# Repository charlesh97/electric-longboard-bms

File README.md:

# Electric Longboard

Archived project. 

Latest revision PDFs
[Schematic](https://gitlab.com/chood2/electric-longboard-bms/-/blob/main/HW/LongboardGaugev2%20SCH.pdf)
[PCB](https://gitlab.com/chood2/electric-longboard-bms/-/blob/main/HW/LongboardGaugev2%20PCB.pdf)

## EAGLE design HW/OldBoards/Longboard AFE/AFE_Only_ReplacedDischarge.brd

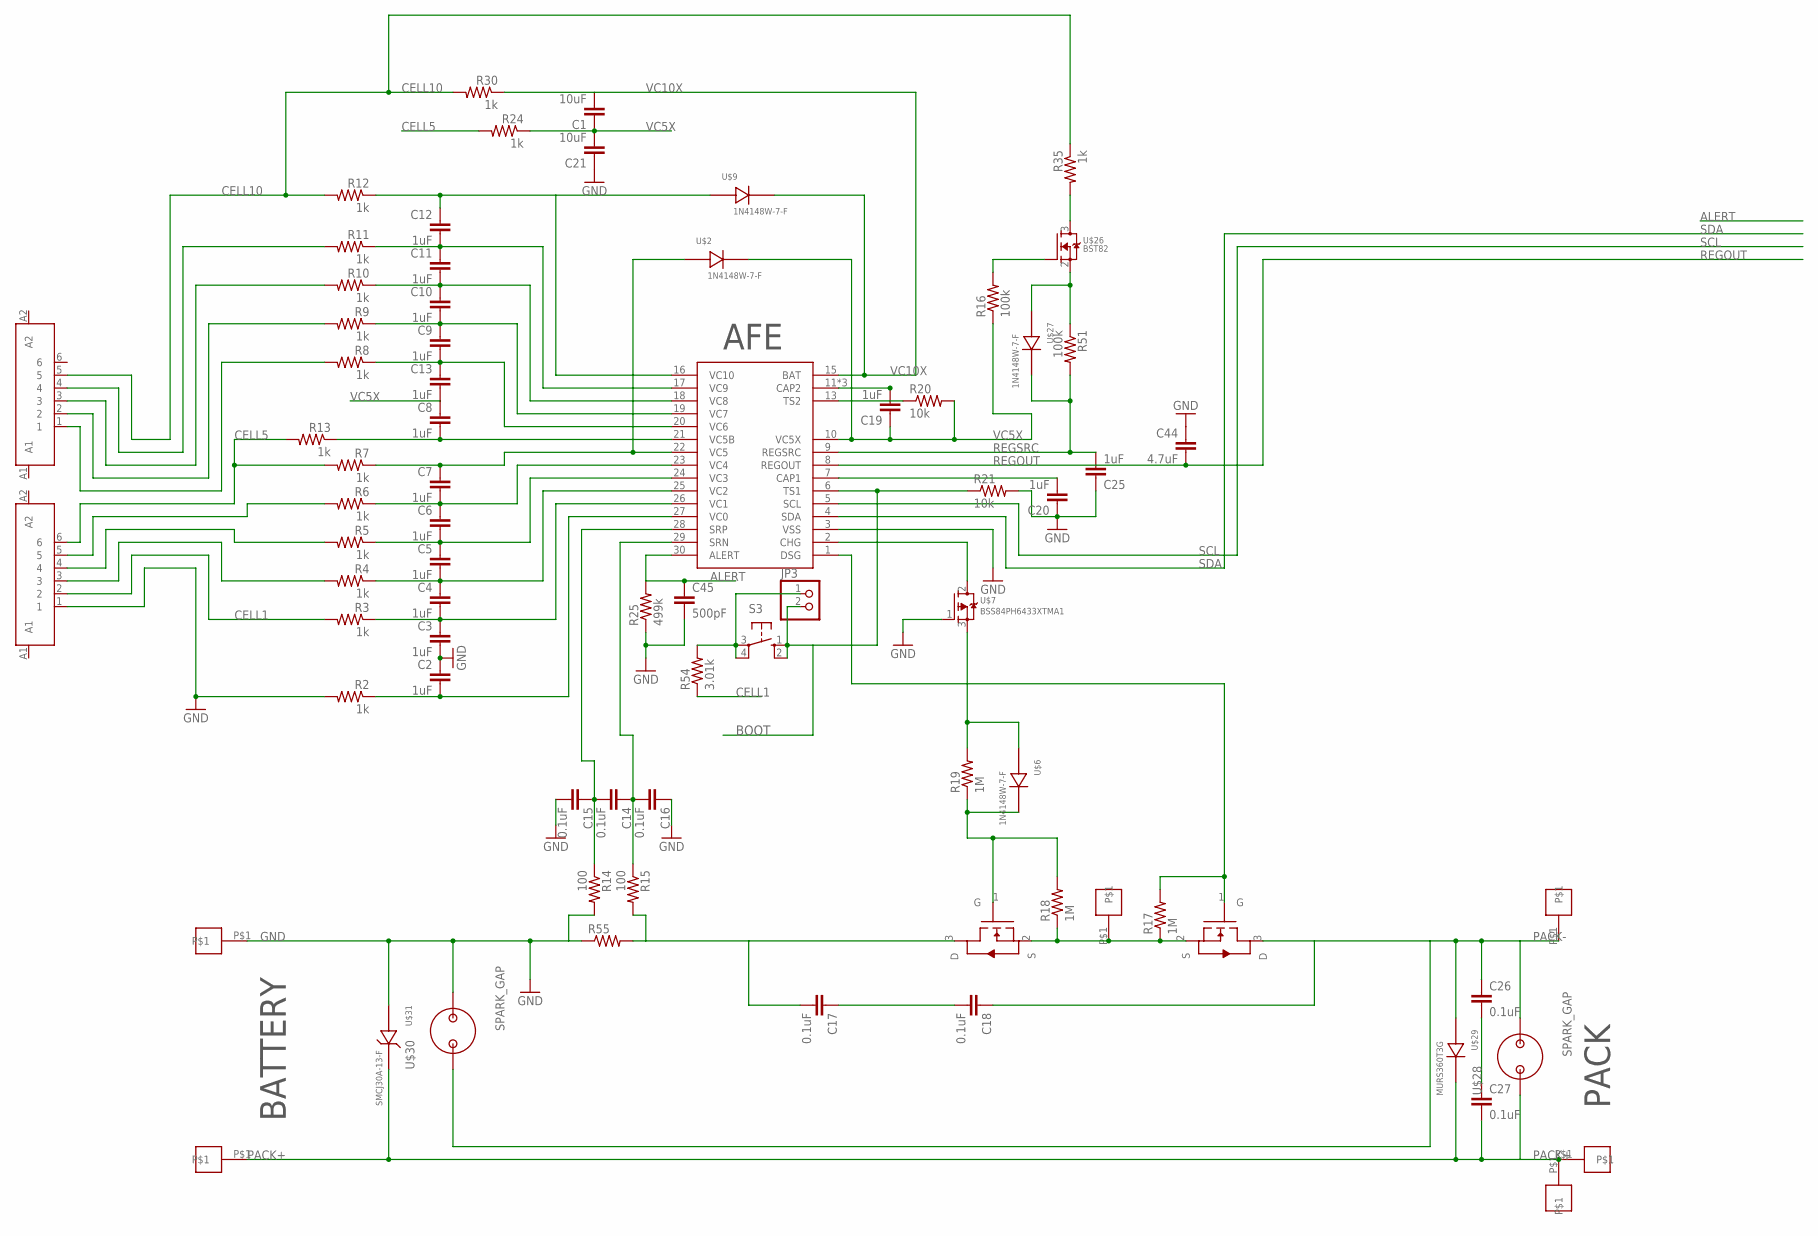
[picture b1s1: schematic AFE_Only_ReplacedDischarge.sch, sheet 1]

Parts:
C1, C21: 10uF; C1210
C2, C3, C4, C5, C6, C7, C8, C9, C10, C11, C12, C13, C19, C20, C25: 1uF; C0805
C14, C15, C16, C17, C18, C26, C27: 0.1uF; C0805
C44: 4.7uF; C0805
C45: 500pF; C0603
JP3: PINHD-1X2; 1X02
R2, R3, R4, R5, R6, R7, R8, R9, R10, R11, R12, R13, R24, R30, R35: 1k; R1206
R14, R15: 100; R0805
R16, R51: 100k; R0805
R17, R18, R19: 1M; R1206
R20, R21: 10k; R0805
R25: 499k; R0603
R54: 3.01k; R1206
R55: R-US_R2512; R2512
S3: 10-XX; B3F-10XX
U$1: BQ76930; SOIC-30
U$2, U$6, U$9, U$27: 1N4148W-7-F; SOD-123
U$3, U$35, U$36, U$37, U$38, U$39: PAD
U$4, U$5: AOB290L; TO-263
U$7: BSS84PH6433XTMA1; SOT23-3
U$24, U$33: JST_6PIN
U$26: BST82; SOT23-3
U$28, U$30: SPARK_GAP
U$29: MURS360T3G; SMC(DO-214AB)
U$31: SMCJ30A-13-F; SMB(DO-214AA)

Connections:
ALERT: C45.1, R25.2, U$1.30 (ALERT); also elsewhere on the board
BOOT: JP3.2, R21.1, S3.1 (S), S3.2 (S1), U$1.6 (TS1)
CELL1: R3.2, R54.1, U$33.2
CELL5: R7.2, R13.2, R24.2, U$33.6
CELL10: R12.2, R30.2, R35.1, U$24.5
CHARGE-: R17.1, R18.1, U$4.2 (S), U$5.2 (S), U$37.P$1
GND: C2.1, C3.2, C15.2, C16.1, C20.1, C21.1, C25.1, C44.1, C45.2, R2.2, R14.2, R21.2, R25.1, R55.1, U$1.3 (VSS), U$3.P$1, U$7.1 (G), U$30.P$2, U$31.P$1 (1), U$33.1; also elsewhere on the board
unnamed: C3.1, C4.2, R3.1, U$1.26 (VC1)
unnamed: C4.1, C5.2, R4.1, U$1.25 (VC2)
unnamed: C5.1, C6.2, R5.1, U$1.24 (VC3)
unnamed: C6.1, C7.2, R6.1, U$1.23 (VC4)
unnamed: C7.1, R7.1, U$1.22 (VC5), U$2.P$1
unnamed: C8.2, R13.1, U$1.21 (VC5B)
unnamed: C9.1, C10.2, R9.1, U$1.19 (VC7)
unnamed: C10.1, C11.2, R10.1, U$1.18 (VC8)
unnamed: C11.1, C12.2, R11.1, U$1.17 (VC9)
unnamed: C12.1, R12.1, U$1.16 (VC10), U$9.P$1
unnamed: R5.2, U$33.4
unnamed: C2.2, R2.1, U$1.27 (VC0)
unnamed: C26.2, C27.1
unnamed: R4.2, U$33.3
unnamed: R6.2, U$33.5
unnamed: R8.2, U$24.1
unnamed: R9.2, U$24.2
unnamed: R10.2, U$24.3
unnamed: R11.2, U$24.4
unnamed: C9.2, C13.1, R8.1, U$1.20 (VC6)
unnamed: R16.2, U$26.1 (G)
unnamed: C20.2, U$1.7 (CAP1)
unnamed: C14.1, C16.2, R15.1, U$1.29 (SRN)
unnamed: JP3.1, R54.2, S3.3, S3.4 (P1)
unnamed: C14.2, C15.1, R14.1, U$1.28 (SRP)
unnamed: R18.2, R19.1, U$5.1 (G), U$6.P$2
unnamed: R19.2, U$6.P$1, U$7.3 (D)
unnamed: U$1.2 (CHG), U$7.2 (S)
unnamed: C17.1, C18.2
unnamed: C19.2, U$1.11 (CAP2), U$1.12 (CAP2), U$1.14 (CAP2)
unnamed: R20.1, U$1.13 (TS2)
unnamed: C17.2, R15.2, R55.2, U$5.3 (D)
unnamed: R17.2, U$1.1 (DSG), U$4.1 (G)
unnamed: R51.1, U$26.2 (S), U$27.P$1
unnamed: R35.2, U$26.3 (D)
PACK+: C27.2, U$28.P$1, U$29.2, U$31.P$2 (2), U$35.P$1, U$36.P$1, U$39.P$1
PACK-: C18.1, C26.1, U$4.3 (D), U$28.P$2, U$29.1, U$30.P$1, U$38.P$1
REGOUT: C44.2, U$1.8 (REGOUT); also elsewhere on the board
REGSRC: C25.2, R51.2, U$1.9 (REGSRC), U$27.P$2
SCL: U$1.5 (SCL); also elsewhere on the board
SDA: U$1.4 (SDA); also elsewhere on the board
VC5X: C1.1, C8.1, C13.2, C19.1, C21.2, R16.1, R20.2, R24.1, U$1.10 (VC5X), U$2.P$2
VC10X: C1.2, R30.1, U$1.15 (BAT), U$9.P$2

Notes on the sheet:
BATTERY
PACK
AFE

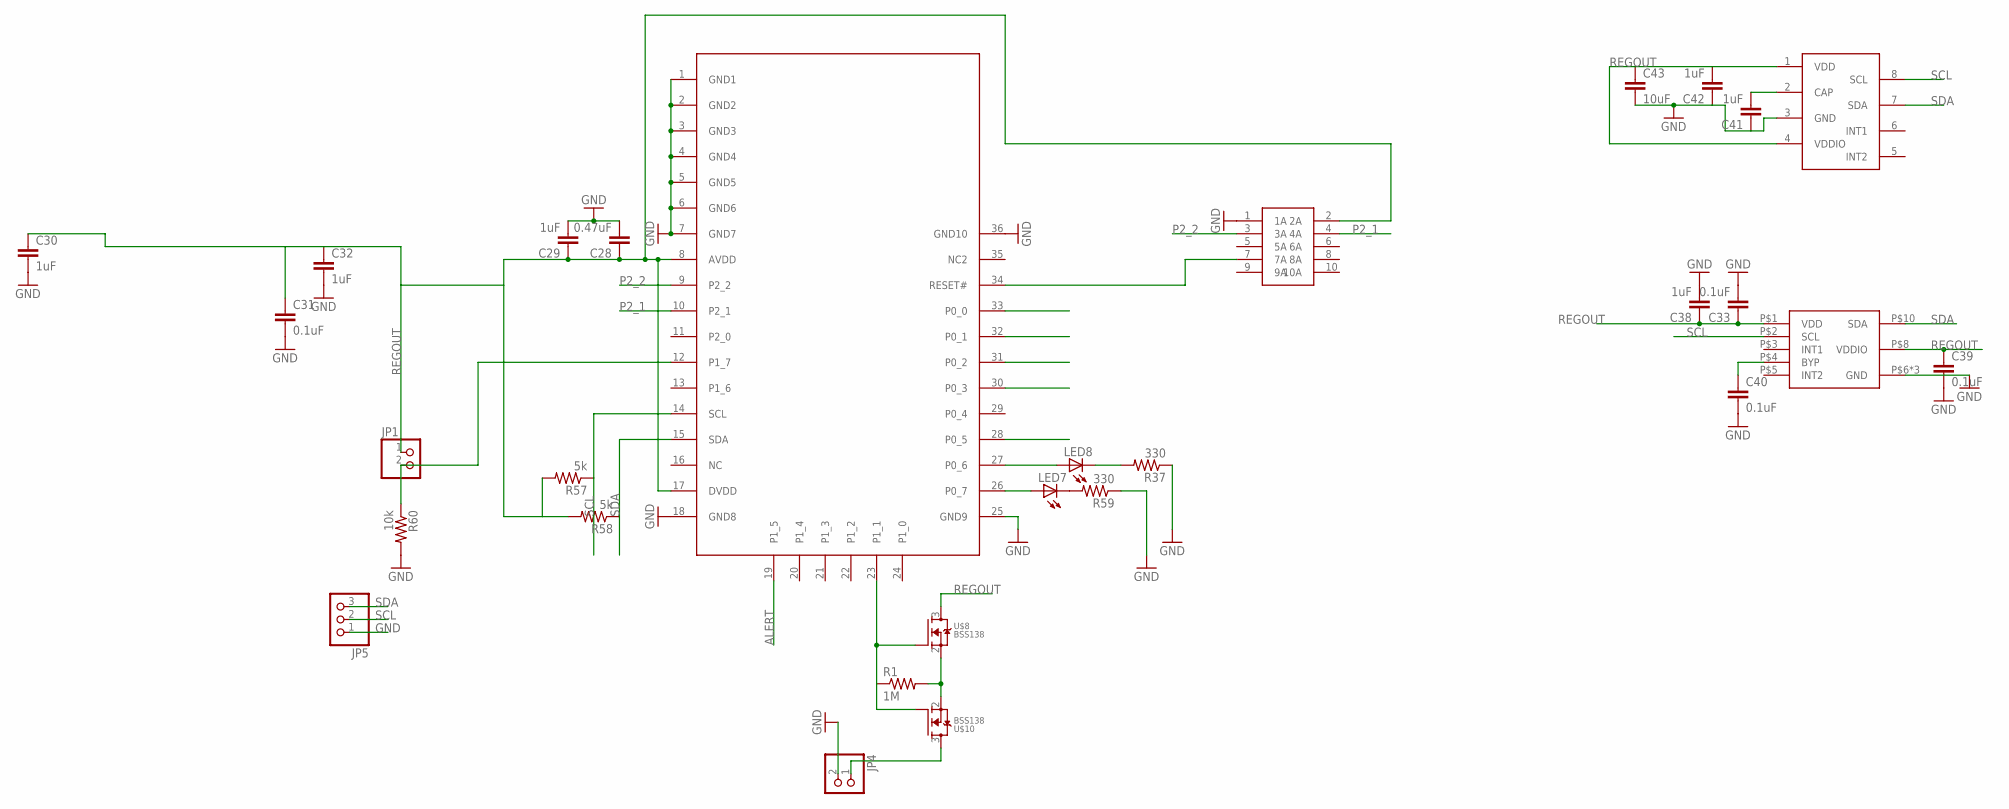
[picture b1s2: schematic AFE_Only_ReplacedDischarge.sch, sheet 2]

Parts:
C28: 0.47uF; C0402
C29, C30, C32, C38, C41, C42: 1uF; C0402
C31, C33, C39, C40: 0.1uF; C0402
C43: 10uF; C0603
JP1, JP4: PINHD-1X2; 1X02
JP5: PINHD-1X3; 1X03
LED7, LED8: LEDCHIP-LED0603; CHIP-LED0603
R1: 1M; R0402
R37, R59: 330; R0402
R57, R58: 5k; R0402
R60: 10k; R0402
U$8, U$10: BSS138; SOT23-3
U$20: BLE113; BLUEGIGA
U$22: RIBBON_10POS_MALE
U$25: MLP3115A2
U$32: MMA8653FC; 10-DFN2X2

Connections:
ALERT: U$20.19 (P1_5); also elsewhere on the board
CARD2: U$20.32 (P0_1)
CD: U$20.33 (P0_0)
CLK: U$20.28 (P0_5)
GND: C28.2, C29.2, C30.2, C31.2, C32.2, C33.2, C38.2, C39.2, C40.2, C41.1, C42.1, C43.2, JP4.2, JP5.1, R37.1, R59.1, R60.2, U$20.1 (GND1), U$20.2 (GND2), U$20.3 (GND3), U$20.4 (GND4), U$20.5 (GND5), U$20.6 (GND6), U$20.7 (GND7), U$20.18 (GND8), U$20.25 (GND9), U$20.36 (GND10), U$22.1 (1A), U$25.3 (GND), U$32.P$6 (GND), U$32.P$7 (GND), U$32.P$9 (GND); also elsewhere on the board
MISO: U$20.31 (P0_2)
MOSI: U$20.30 (P0_3)
unnamed: LED8.A, U$20.27 (P0_6)
unnamed: LED8.C, R37.2
unnamed: R1.1, U$8.1 (G), U$10.1 (G), U$20.23 (P1_1)
unnamed: JP4.1, U$10.3 (D)
unnamed: R1.2, U$8.2 (S), U$10.2 (S)
unnamed: LED7.A, U$20.26 (P0_7)
unnamed: JP1.2, R60.1, U$20.12 (P1_7)
unnamed: LED7.C, R59.2
unnamed: U$20.34 (RESET#), U$22.7 (7A)
unnamed: C41.2, U$25.2 (CAP)
unnamed: C40.1, U$32.P$4 (BYP)
P2_1: U$20.10 (P2_1), U$22.4 (4A)
P2_2: U$20.9 (P2_2), U$22.3 (3A)
REGOUT: C28.1, C29.1, C30.1, C31.1, C32.1, C33.1, C38.1, C39.1, C42.2, C43.1, JP1.1, R57.2, R58.2, U$8.3 (D), U$20.8 (AVDD), U$20.17 (DVDD), U$22.2 (2A), U$25.1 (VDD), U$25.4 (VDDIO), U$32.P$1 (VDD), U$32.P$8 (VDDIO); also elsewhere on the board
SCL: JP5.2, R57.1, U$20.14 (SCL), U$25.8 (SCL), U$32.P$2 (SCL); also elsewhere on the board
SDA: JP5.3, R58.1, U$20.15 (SDA), U$25.7 (SDA), U$32.P$10 (SDA); also elsewhere on the board

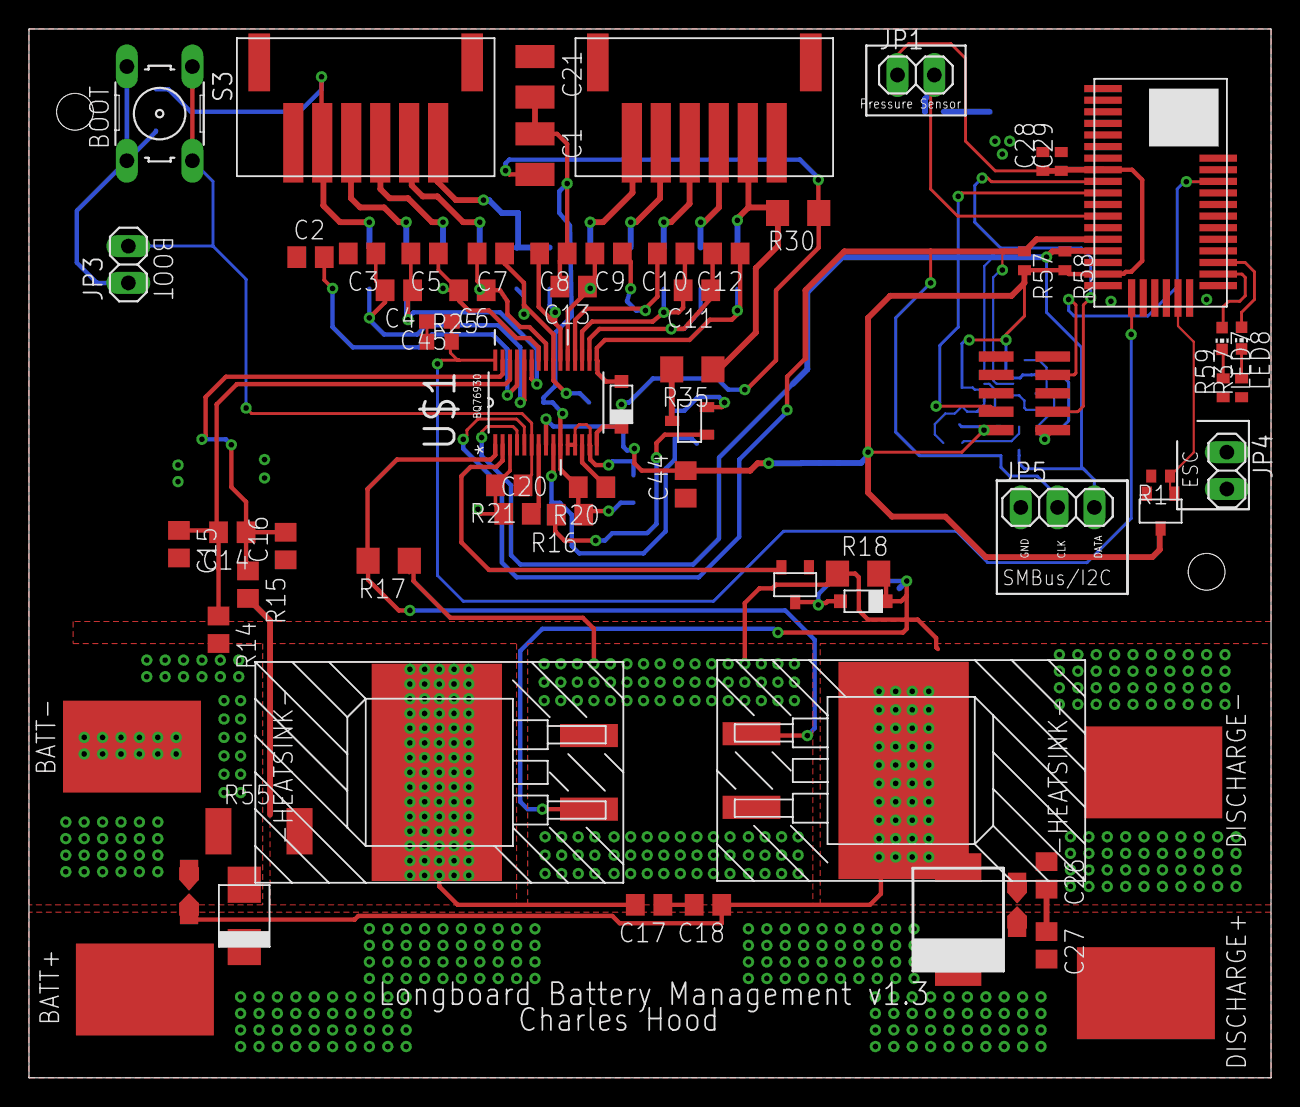
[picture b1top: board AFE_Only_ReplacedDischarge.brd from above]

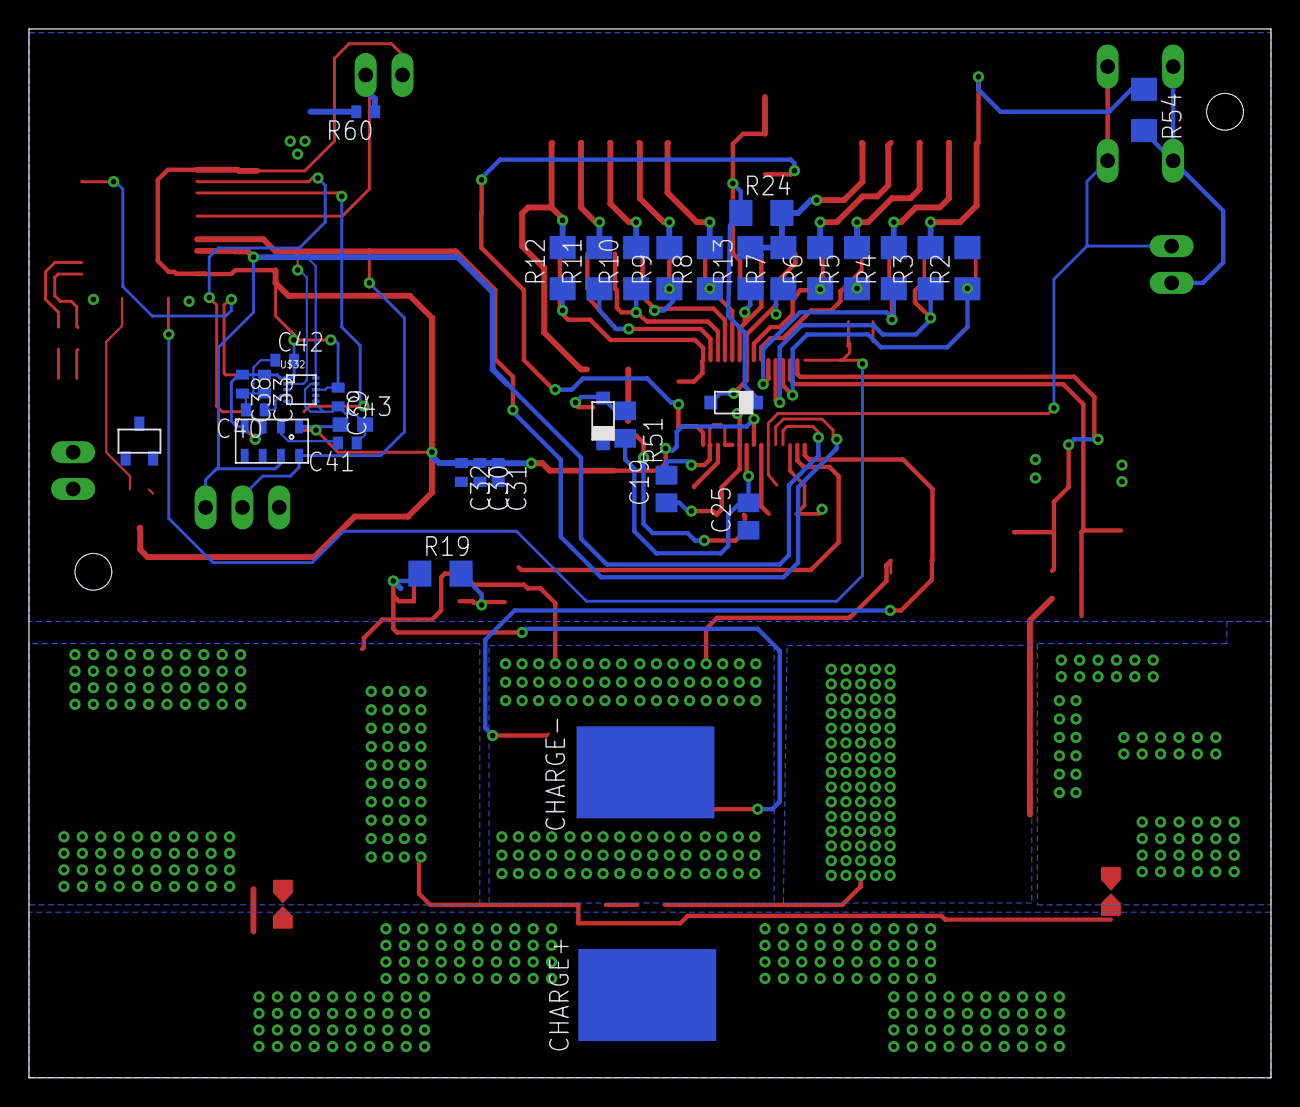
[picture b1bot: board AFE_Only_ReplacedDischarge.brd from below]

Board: 2 copper layers, 85.7 x 72.4 mm, 105 parts (36 on the bottom side), 63 nets.

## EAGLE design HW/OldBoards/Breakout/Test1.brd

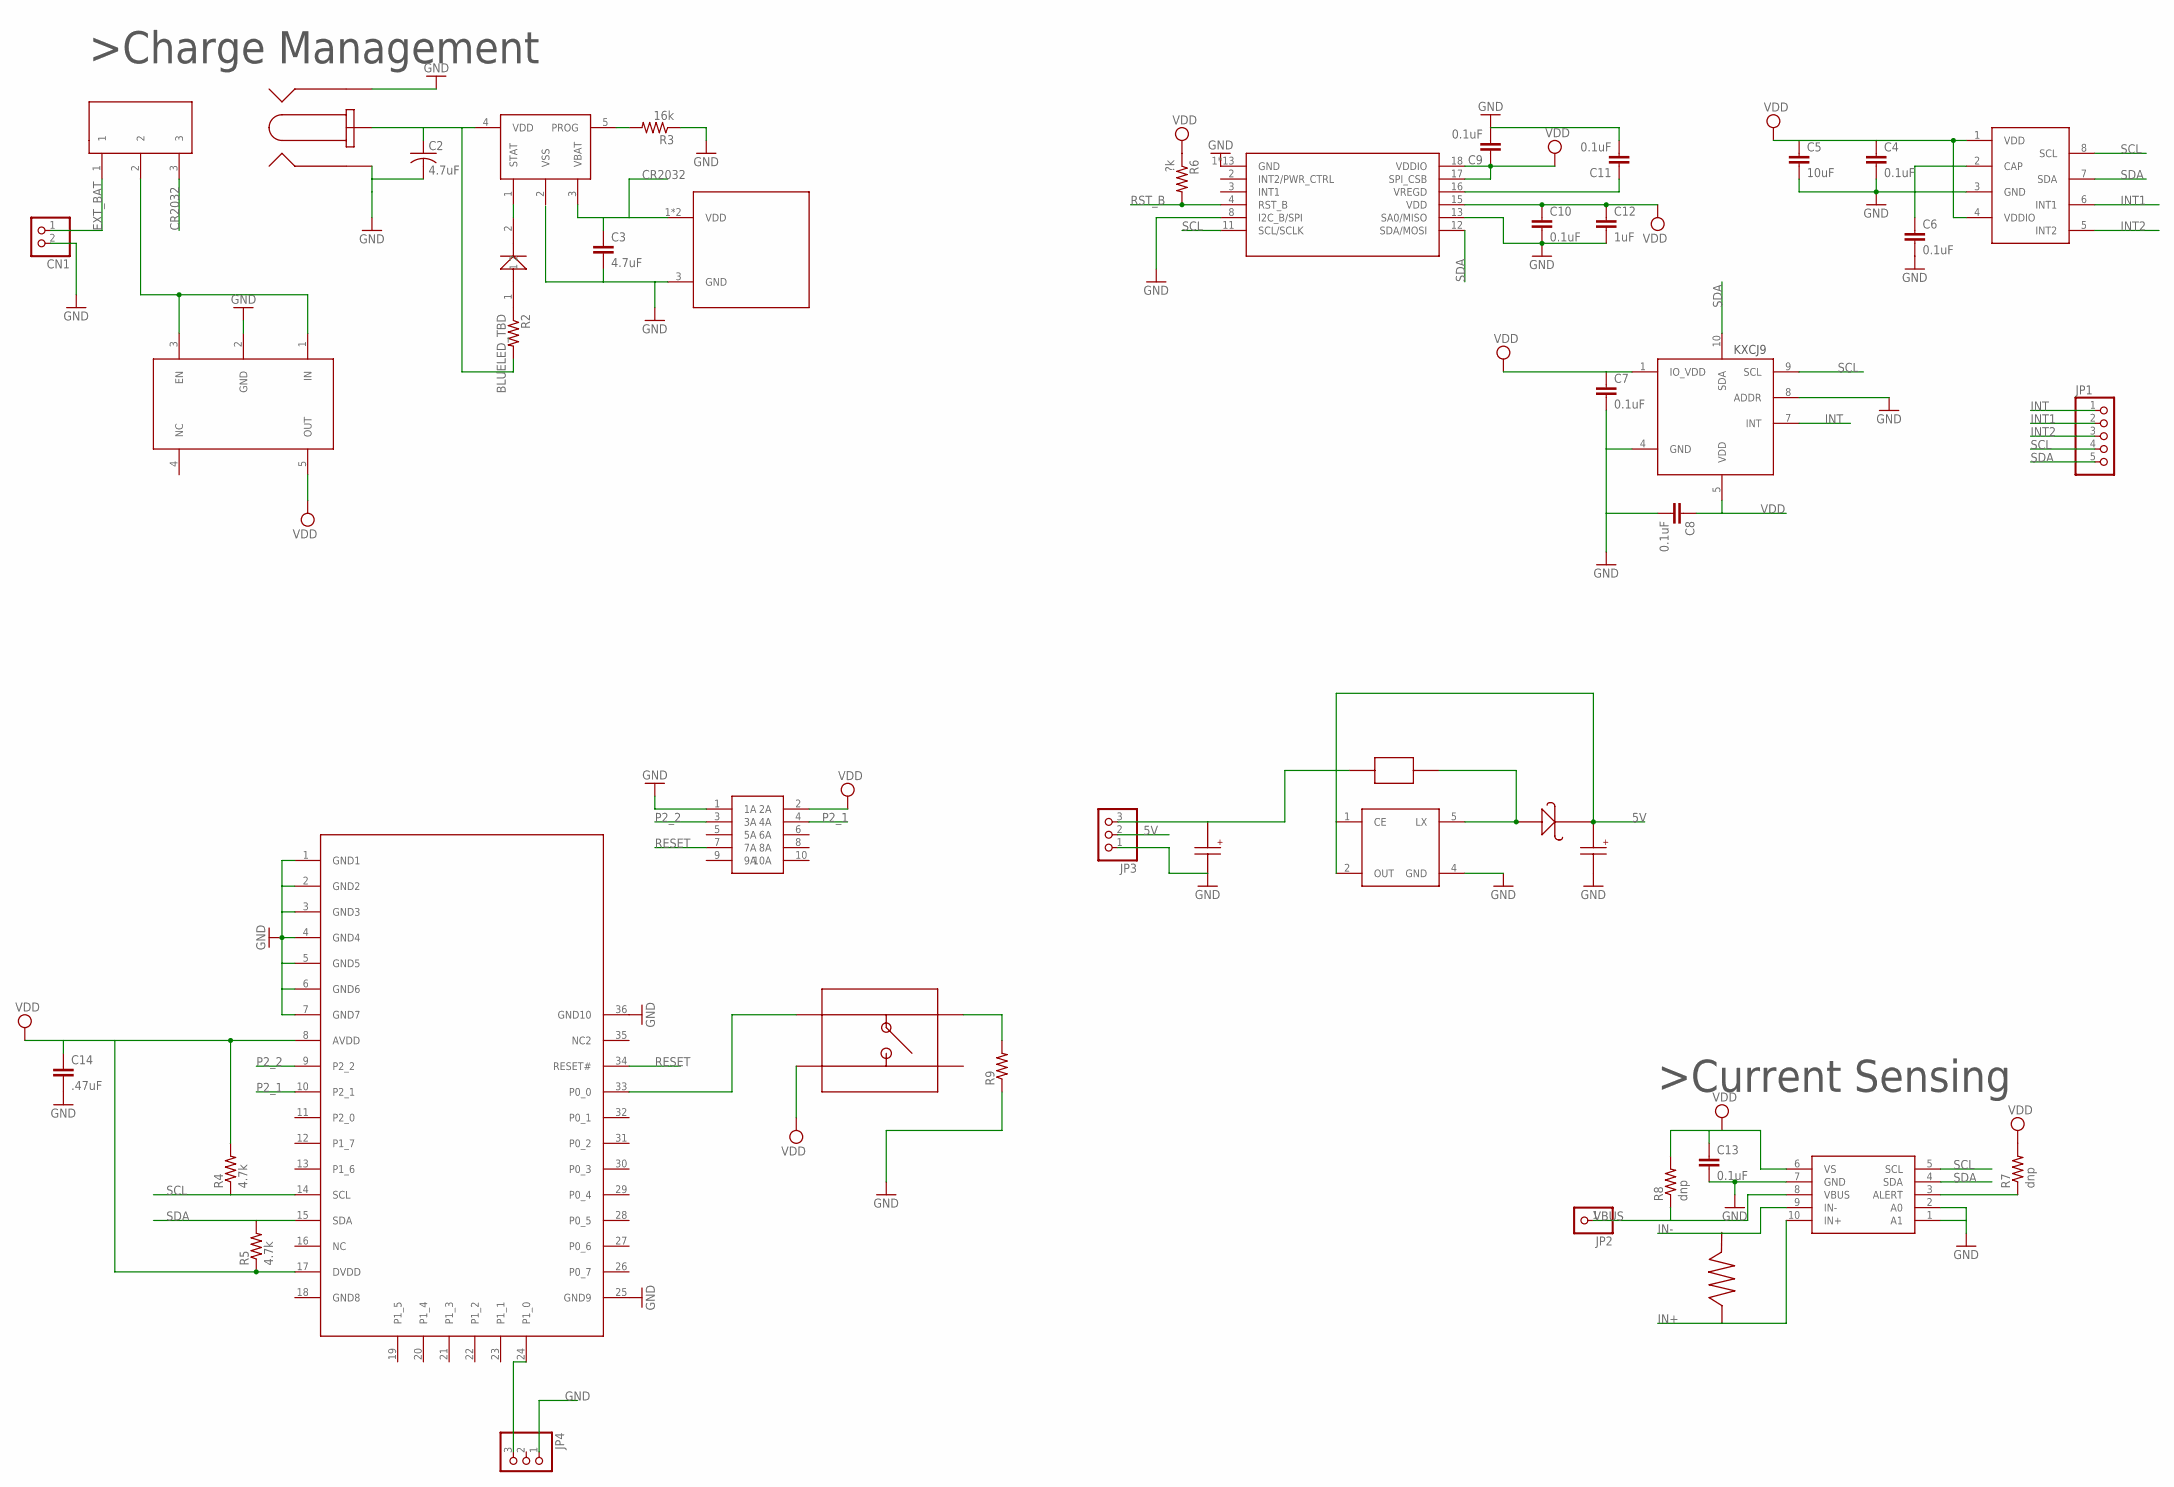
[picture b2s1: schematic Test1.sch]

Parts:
C2: 4.7uF; C0603
C3: 4.7uF; C0402
C4, C6, C7, C8, C9, C10, C11, C13: 0.1uF; C0402
C5: 10uF; C0402
C12: 1uF; C0402
C14: .47uF; C0402
CN1: JST_2PIN-THM; JST-PH-2-THM
JP1: PINHD-1X5; 1X05
JP2: PINHD-1X1; 1X01
JP3: PINHD-1X3; 1X03
JP4: PINHD-1X3/90; 1X03/90
R2: BLUELED_TBD; R0402
R3: 16k; R0402
R4, R5: 4.7k; R0402
R6: ?k; R0402
R7, R8: dnp; R0402
R9: R-US_R0402; R0402
U$1: BAT-HLD-001
U$2: INA226
U$3: FXAS21002
U$4: PJ-040
U$5: PTS840
U$6: CD54NP-470LC
U$7: MRB0520LT1G; SOD-323F
U$8: MIC5203; SOT23-5L
U$9: MLP3115A2
U$10: RIBBON_10POS_MALE
U$11: BLE113; BLUEGIGA
U$12: SPDT_THRU
U$13: KXCJ9
U$14: LTST-C190KRKT
U$15: ERJ-MS6SFM50U
U$16: MCP73831
U$17: NCP1402; SOT23-5L
U$18: 10uF; C2413
U$19: 68uF; C2413

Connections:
5V: JP3.2, U$7.2, U$17.1 (CE), U$17.2 (OUT), U$19.1
CR2032: C3.1, U$1.1 (VDD), U$1.2 (VDD), U$12.3, U$16.3 (VBAT)
EXT_BAT: CN1.1 (2), U$12.1
GND: C2.2, C3.2, C4.2, C5.2, C6.2, C7.2, C8.2, C9.2, C10.2, C11.2, C12.2, C13.2, C14.2, CN1.2 (1), JP3.1, JP4.1, R3.1, R9.1, U$1.3 (GND), U$2.1 (A1), U$2.2 (A0), U$2.7 (GND), U$3.1 (GND), U$3.5 (GND), U$3.6 (GND), U$3.7 (GND), U$3.8 (I2C_B/SPI), U$3.9 (GND), U$3.10 (GND), U$3.13 (SA0/MISO), U$3.14 (GND), U$3.19 (GND), U$3.20 (GND), U$3.21 (GND), U$3.22 (GND), U$3.23 (GND), U$3.24 (GND), U$4.2, U$4.3, U$8.2 (GND), U$9.3 (GND), U$10.1 (1A), U$11.1 (GND1), U$11.2 (GND2), U$11.3 (GND3), U$11.4 (GND4), U$11.5 (GND5), U$11.6 (GND6), U$11.7 (GND7), U$11.25 (GND9), U$11.36 (GND10), U$13.4 (GND), U$13.8 (ADDR), U$17.4 (GND), U$18.2, U$19.2
IN+: U$2.10 (IN+), U$15.1
IN-: U$2.9 (IN-), U$15.2
INT: JP1.1, U$13.7 (INT)
INT1: JP1.2, U$9.6 (INT1)
INT2: JP1.3, U$9.5 (INT2)
unnamed: JP4.3, U$11.24 (P1_0)
unnamed: C2.1, R2.2, U$4.1, U$16.4 (VDD)
unnamed: U$14.2, U$16.1 (STAT)
unnamed: R2.1, U$14.1
unnamed: R3.2, U$16.5 (PROG)
unnamed: C6.1, U$9.2 (CAP)
unnamed: C11.1, U$3.16 (VREGD)
unnamed: U$8.1 (IN), U$8.3 (EN), U$12.2
unnamed: U$5.4, U$11.33 (P0_0)
unnamed: R9.2, U$5.3
unnamed: R7.1, U$2.3 (ALERT)
unnamed: JP3.3, U$6.1, U$18.1
unnamed: U$6.2, U$7.1, U$17.5 (LX)
P2_1: U$10.4 (4A), U$11.10 (P2_1)
P2_2: U$10.3 (3A), U$11.9 (P2_2)
RESET: U$10.7 (7A), U$11.34 (RESET#)
RST_B: R6.2, U$3.4 (RST_B)
SCL: JP1.4, R4.1, U$2.5 (SCL), U$3.11 (SCL/SCLK), U$9.8 (SCL), U$11.14 (SCL), U$13.9 (SCL)
SDA: JP1.5, R5.2, U$2.4 (SDA), U$3.12 (SDA/MOSI), U$9.7 (SDA), U$11.15 (SDA), U$13.10 (SDA)
VBUS: JP2.1, R8.1, U$2.8 (VBUS)
VDD: C4.1, C5.1, C7.1, C8.1, C9.1, C10.1, C12.1, C13.1, C14.1, R4.2, R5.1, R6.1, R7.2, R8.2, U$2.6 (VS), U$3.15 (VDD), U$3.17 (SPI_CSB), U$3.18 (VDDIO), U$5.2, U$8.5 (OUT), U$9.1 (VDD), U$9.4 (VDDIO), U$10.2 (2A), U$11.8 (AVDD), U$11.17 (DVDD), U$13.1 (IO_VDD), U$13.5 (VDD)

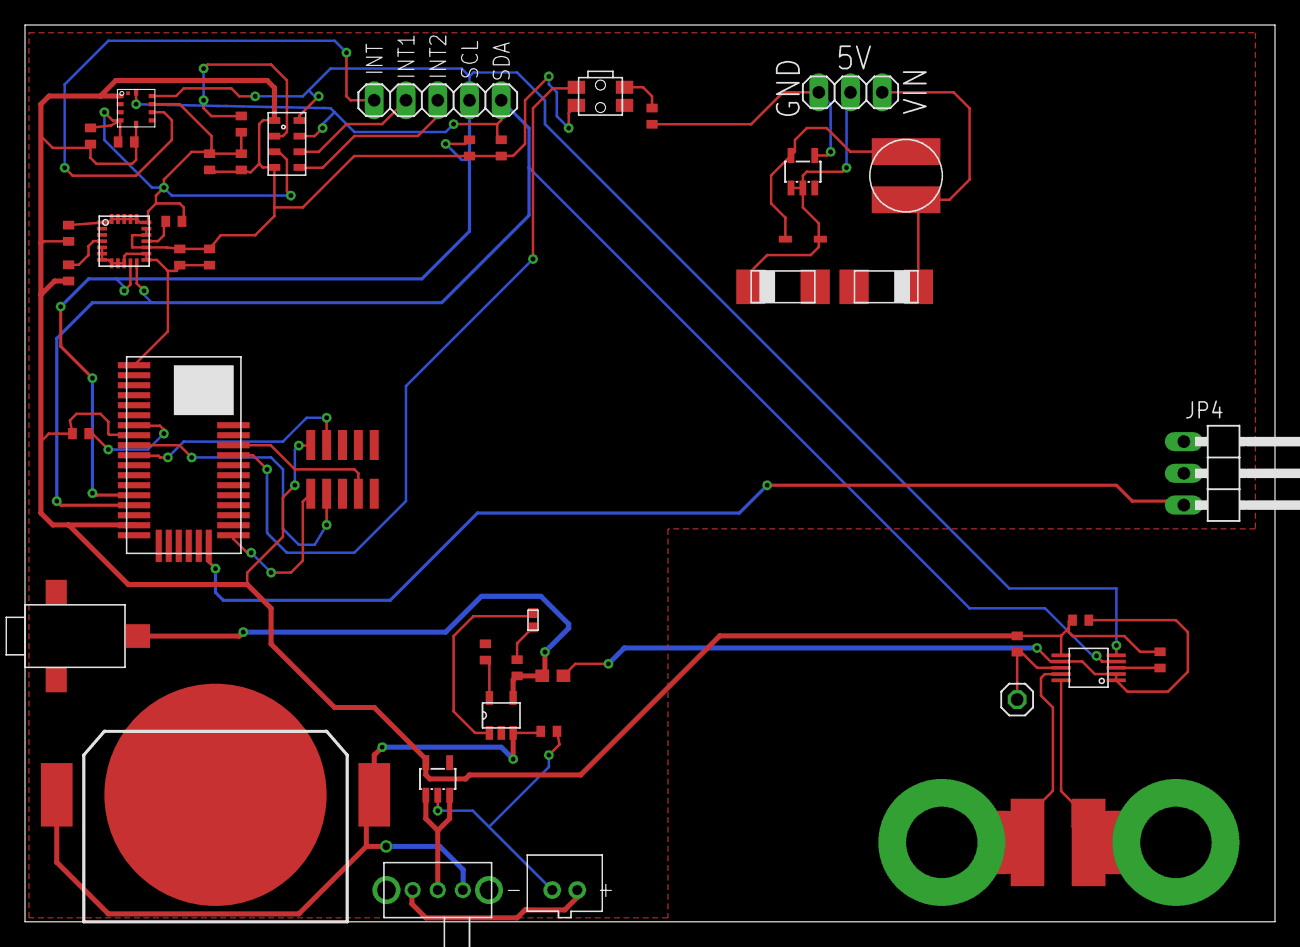
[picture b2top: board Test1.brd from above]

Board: 2 copper layers, 100.0 x 71.7 mm, 45 parts (0 on the bottom side), 30 nets.

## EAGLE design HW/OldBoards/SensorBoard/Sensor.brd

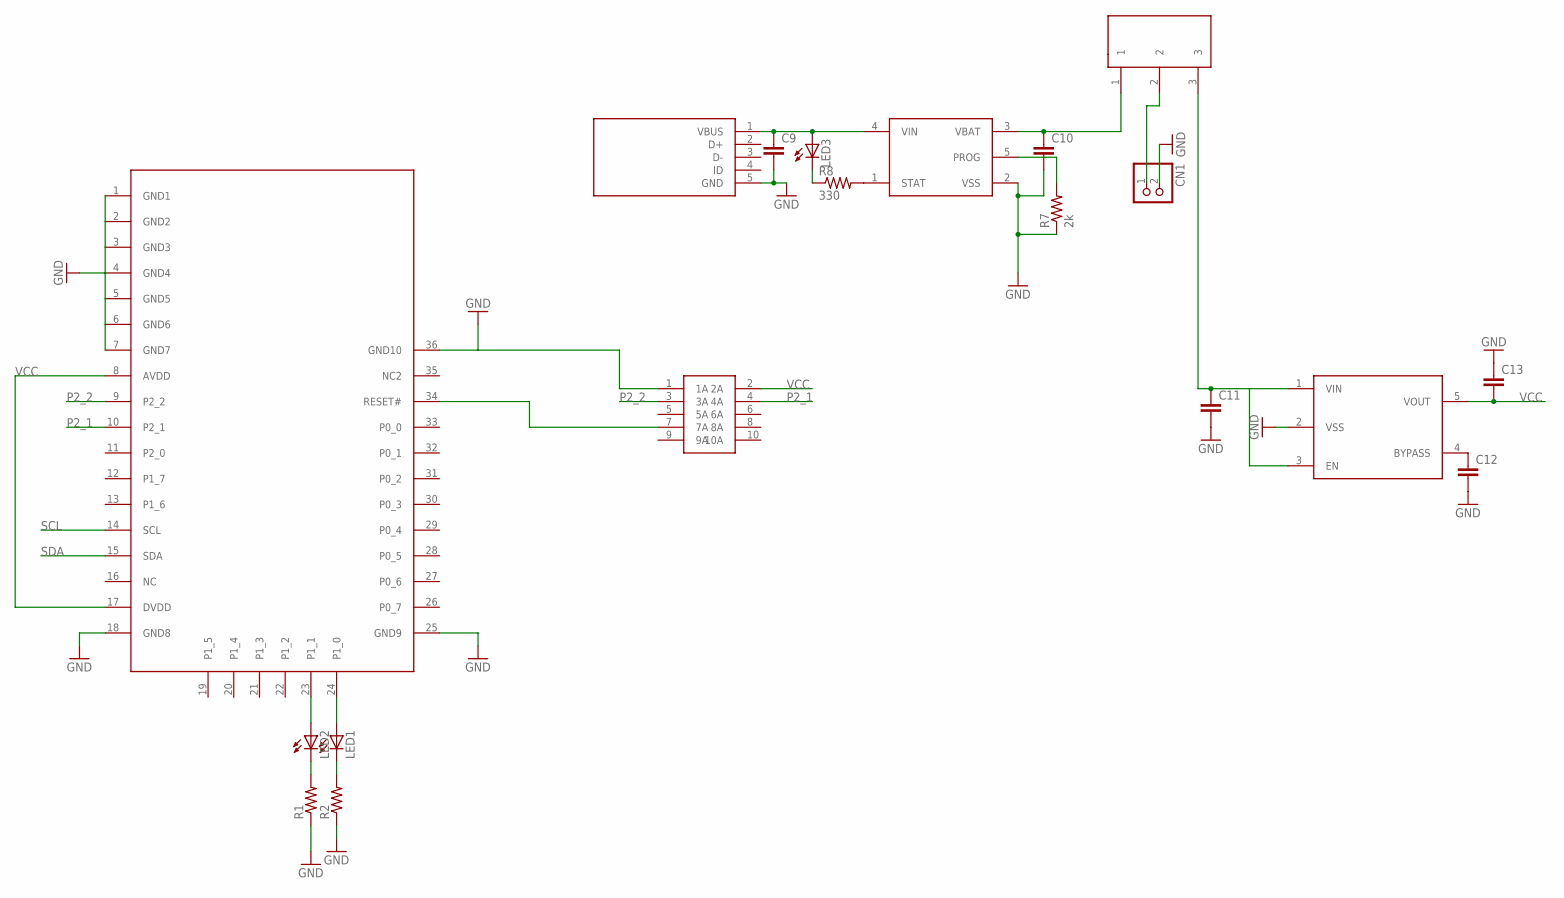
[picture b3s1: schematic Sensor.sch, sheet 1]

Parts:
C9, C10, C11, C12, C13: C-EUC0402; C0402
CN1: JST_2PIN-THM; JST-PH-2-THM
LED1, LED2, LED3: LEDCHIP-LED0805; CHIP-LED0805
R1, R2: R-US_R0402; R0402
R7: 2k; R0402
R8: 330; R0402
U$1: BLE113; BLUEGIGA
U$2: MCP73831; SOT23-5L
U$8: RIBBON_10POS_MALE
U$9: SPDT_THRU
U$10: USB_MINI
U$11: LP3985; SOT23-5L

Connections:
GND: C9.2, C10.2, C11.2, C12.2, C13.1, CN1.2 (1), R1.1, R2.1, R7.1, U$1.1 (GND1), U$1.2 (GND2), U$1.3 (GND3), U$1.4 (GND4), U$1.5 (GND5), U$1.6 (GND6), U$1.7 (GND7), U$1.18 (GND8), U$1.25 (GND9), U$1.36 (GND10), U$2.2 (VSS), U$8.1 (1A), U$10.5 (GND), U$11.2 (VSS); also elsewhere on the board
unnamed: C9.1, LED3.A, U$2.4 (VIN), U$10.1 (VBUS)
unnamed: C10.1, U$2.3 (VBAT), U$9.1
unnamed: C11.1, U$9.3, U$11.1 (VIN), U$11.3 (EN)
unnamed: U$1.34 (RESET#), U$8.7 (7A)
unnamed: LED2.C, R1.2
unnamed: LED1.C, R2.2
unnamed: LED1.A, U$1.24 (P1_0)
unnamed: LED2.A, U$1.23 (P1_1)
unnamed: CN1.1 (2), U$9.2
unnamed: R7.2, U$2.5 (PROG)
unnamed: C12.1, U$11.4 (BYPASS)
unnamed: R8.2, U$2.1 (STAT)
unnamed: LED3.C, R8.1
P2_1: U$1.10 (P2_1), U$8.4 (4A)
P2_2: U$1.9 (P2_2), U$8.3 (3A)
SCL: U$1.14 (SCL); also elsewhere on the board
SDA: U$1.15 (SDA); also elsewhere on the board
VCC: C13.2, U$1.8 (AVDD), U$1.17 (DVDD), U$8.2 (2A), U$11.5 (VOUT); also elsewhere on the board

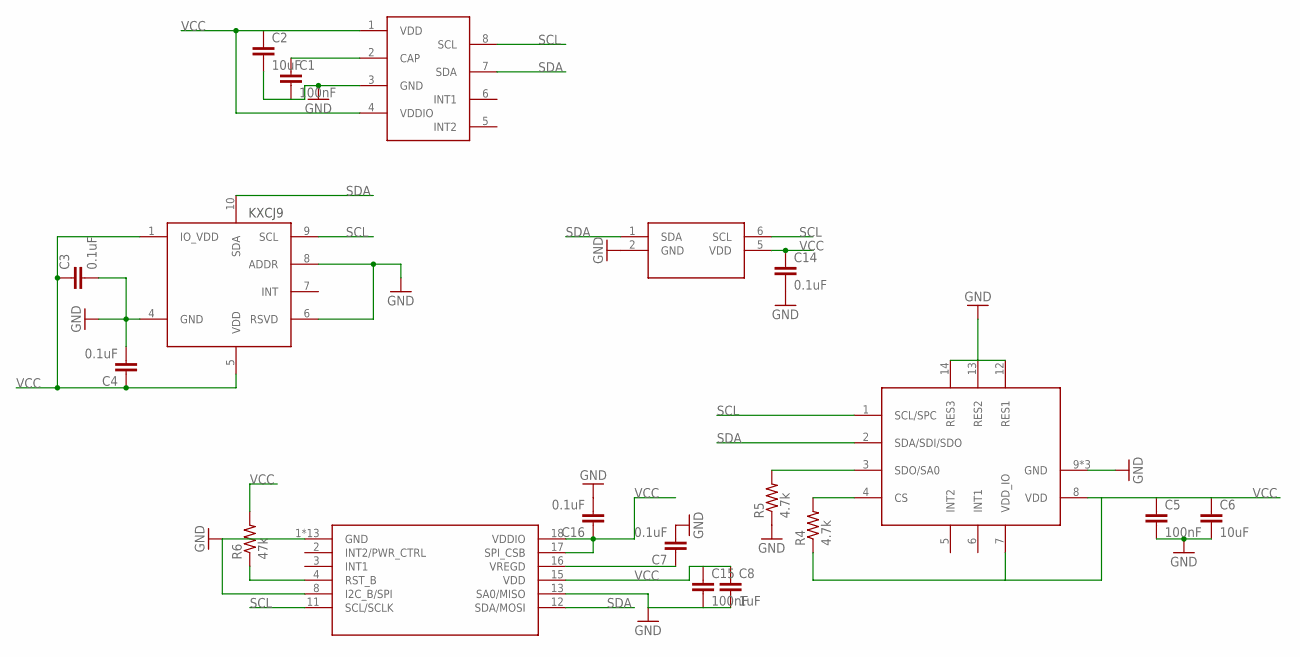
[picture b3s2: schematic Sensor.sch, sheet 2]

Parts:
ACCEL_16: LISDH_16G; LGA14_2X2
C1, C5, C15: 100nF; C0402
C2, C6: 10uF; C0402
C3, C4, C7, C14, C16: 0.1uF; C0402
C8: 1uF; C0402
R4, R5: 4.7k; R0402
R6: 47k; R0402
U$12: KXCJ9
U$13: MLP3115A2
U$14: FXAS21002
U$15: SI7021-A20

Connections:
GND: ACCEL_16.9 (GND), ACCEL_16.10 (GND), ACCEL_16.11 (GND), ACCEL_16.12 (RES1), ACCEL_16.13 (RES2), ACCEL_16.14 (RES3), C1.2, C2.2, C3.2, C4.2, C5.2, C6.2, C7.2, C8.2, C14.2, C15.2, C16.2, R5.1, U$12.4 (GND), U$12.6 (RSVD), U$12.8 (ADDR), U$13.3 (GND), U$14.1 (GND), U$14.5 (GND), U$14.6 (GND), U$14.7 (GND), U$14.8 (I2C_B/SPI), U$14.9 (GND), U$14.10 (GND), U$14.13 (SA0/MISO), U$14.14 (GND), U$14.19 (GND), U$14.20 (GND), U$14.21 (GND), U$14.22 (GND), U$14.23 (GND), U$14.24 (GND), U$15.2 (GND); also elsewhere on the board
unnamed: C1.1, U$13.2 (CAP)
unnamed: ACCEL_16.4 (CS), R4.2
unnamed: ACCEL_16.3 (SDO/SA0), R5.2
unnamed: R6.1, U$14.4 (RST_B)
unnamed: C7.1, U$14.16 (VREGD)
SCL: ACCEL_16.1 (SCL/SPC), U$12.9 (SCL), U$13.8 (SCL), U$14.11 (SCL/SCLK), U$15.6 (SCL); also elsewhere on the board
SDA: ACCEL_16.2 (SDA/SDI/SDO), U$12.10 (SDA), U$13.7 (SDA), U$14.12 (SDA/MOSI), U$15.1 (SDA); also elsewhere on the board
VCC: ACCEL_16.7 (VDD_IO), ACCEL_16.8 (VDD), C2.1, C3.1, C4.1, C5.1, C6.1, C8.1, C14.1, C15.1, C16.1, R4.1, R6.2, U$12.1 (IO_VDD), U$12.5 (VDD), U$13.1 (VDD), U$13.4 (VDDIO), U$14.15 (VDD), U$14.17 (SPI_CSB), U$14.18 (VDDIO), U$15.5 (VDD); also elsewhere on the board

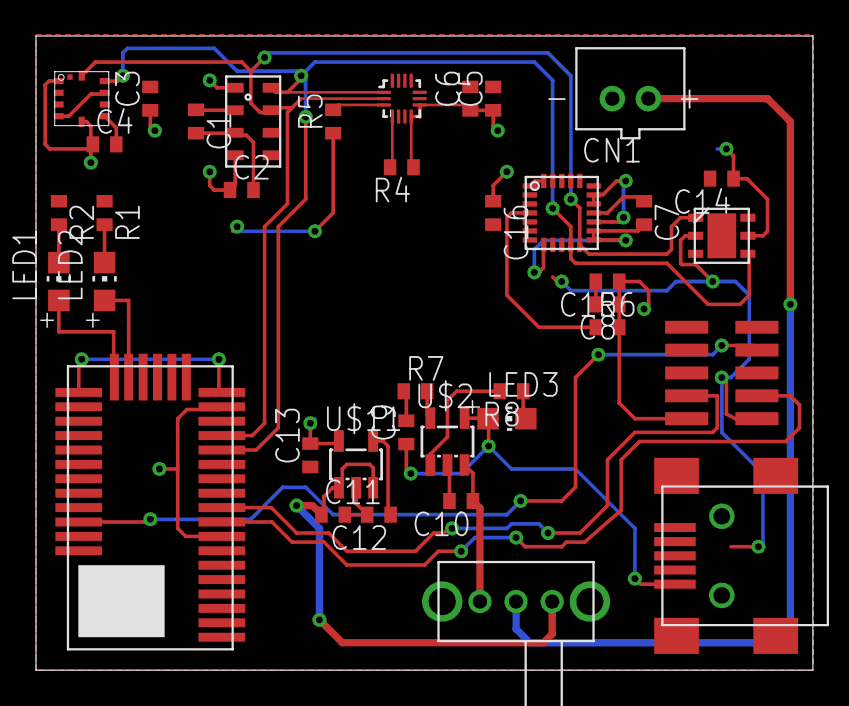
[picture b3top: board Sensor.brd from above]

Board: 2 copper layers, 43.2 x 35.2 mm, 38 parts (0 on the bottom side), 24 nets.

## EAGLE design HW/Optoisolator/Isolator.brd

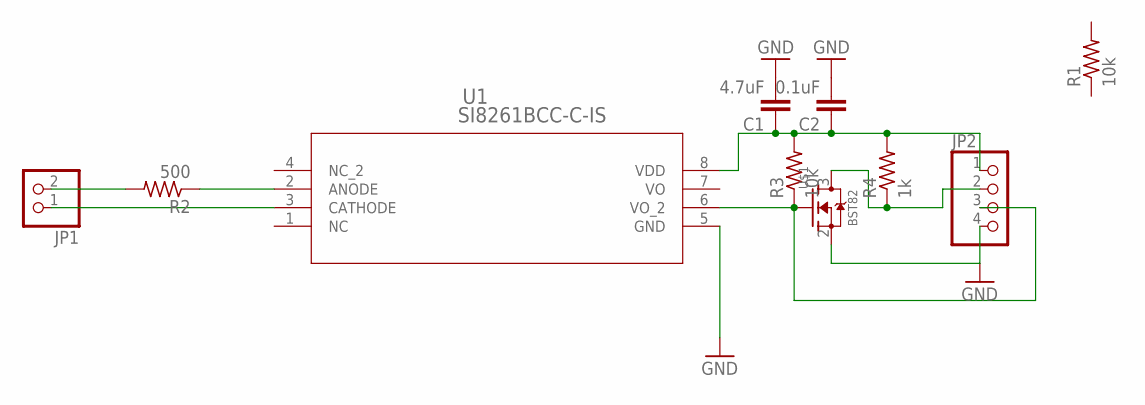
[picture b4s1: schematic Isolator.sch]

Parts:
C1: 4.7uF; C0402
C2: 0.1uF; C0402
JP1: PINHD-1X2; 1X02
JP2: PINHD-1X4; 1X04
R1, R3: 10k; R0402
R2: 500; R0402
R4: 1k; R0402
U1: SI8261BCC-C-IS; SOIC_8_127MM
U$1: BST82; SOT23-3

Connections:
GND: C1.2, C2.2, JP2.4, U1.5 (GND), U$1.2 (S)
unnamed: C1.1, C2.1, JP2.1, R3.2, R4.2, U1.8 (VDD)
unnamed: JP2.3, R3.1, U1.6 (VO_2), U$1.1 (G)
unnamed: JP1.2, R2.2
unnamed: JP2.2, R4.1, U$1.3 (D)
unnamed: R2.1, U1.2 (ANODE)
unnamed: JP1.1, U1.3 (CATHODE)

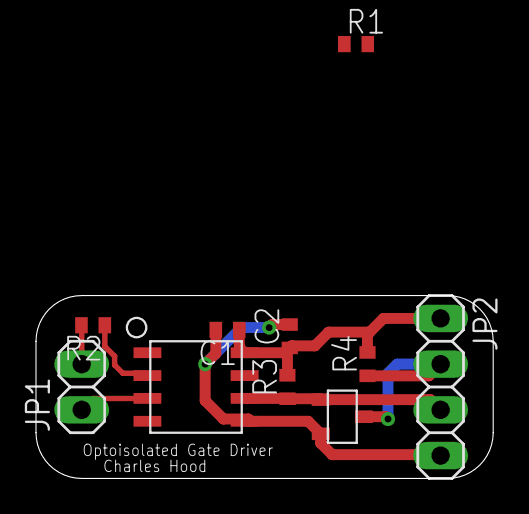
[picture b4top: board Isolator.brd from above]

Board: 2 copper layers, 25.4 x 10.2 mm, 10 parts (0 on the bottom side), 7 nets.

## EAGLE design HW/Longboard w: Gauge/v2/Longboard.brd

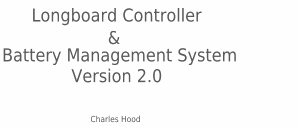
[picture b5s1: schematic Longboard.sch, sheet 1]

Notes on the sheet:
Longboard Controller
Battery Management System
Version 2.0
Charles Hood

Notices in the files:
parts and their libraries:
Tag-Connect-Footprints: ©2009 ROFA.cz - modified and updated by Robert Darlington ‹rdarlington@gmail.com›
SparkFun-Connectors: Licensing: Creative Commons ShareAlike 4.0 International - https://creativecommons.org/licenses/by-sa/4.0
